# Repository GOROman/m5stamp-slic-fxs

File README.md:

# m5stamp-slic-fxs — SLIC2PORT-FXS

**ステータス: 基板 v4.0（4層・全面再レイアウト・KiCad 配線済み）が最新。未発注。2026-10-31 時点**

**v4.0** は、v3.4.2 の電気的中身（回路・ネット・156 部品）をそのままに、配置を全面刷新して **4 層化**（F.Cu 信号 / In1.Cu GND プレーン / In2.Cu 信号 / B.Cu 信号）し、KiCad 上で配線まで完遂した版です。機能ブロック構成（ポート A/B を左右対称に、SLIC は自ポート近く、リレーは同一方向に整列、Stamp は中央＋アンテナキープアウト）で、FreeRouting + 手仕上げにより**未接続 0・短絡 0**。DRC の残件はフットプリント固有の裁定済み項目のみです。製造用 Gerber は KiCad 出力の一式を `gerber/` に同梱しています。**推奨ソルダーマスク色はマットブラック**（発注時に選択）。シルクにはタイトルブロック「SLIC2PORT-FXS Rev 4.0 / @GOROman / 2026-10-31」、大型部品の機能名ラベル、回線系エリアへの高圧警告マークを入れ、ロゴは決定後に差し替えできるよう配置スペースを確保しています。詳細は `kicad/CAD_REPORT.md` 第11ラウンド参照。

v3.4 は第7ラウンドの全数監査（物理干渉・シルク・ファームウェア整合・電気的妥当性・製造性・調達整合・極性）を通過して EasyEDA で配線した版（配線率 100%、トラック 1,514 本・ビア 179 本）、v3.4.1 は発注前チェック（Issue #9・#12）の是正版、v3.4.2 は RJ11 を秋月 100954（Neltron 7002-XPXC）のメーカー図面で全面是正し C13 のパッド干渉を解消した版です。各版の経緯は `kicad/CAD_REPORT.md` 第7〜第10ラウンドと Git 履歴を参照してください。v3.4 の EasyEDA 配線データ（`gerber/SLIC2PORT-FXS-v3.4.epro2` 等）は履歴として残しています。

## 概要

FAX機（Canon PIXUS MX923）と PC の FAXモデム（または2台目の FAX/電話機）を、公衆回線なしで直接 T.30 通信させるための、M5Stamp 制御の **2ポート疑似交換機（FXS 回線シミュレータ）** 基板の設計プロジェクト。

- SLICモジュール **KS0835F（Silvertel AG1171 系）×2** をソケット搭載し、各ポートが独立した加入者回線として振る舞う（回線電圧供給・リング送出/リングトリップ・オフフック検出）
- 制御は **M5StampS3（ESP32-S3）**：状態機械（発信/呼出/接続/解放）、ADC による音声モニタ＋DTMF（Goertzel）検出、トーン生成
- 音声のクロス接続は **Omron G5V-2 リレー×2**（DPDT）。無励磁（フェイルセーフ）で相手ポートと相互接続、励磁でトーンバスに切り替わる
- 信号レベルの不整合（SLIC 5V 系 ⇔ ESP32-S3 3.3V 系）は **74HCT244** のレベル変換と SHK 分圧で吸収
- ポートAに FAX機、ポートBにモデムを RJ11 で挿すだけで相互に発着信でき、T.30 ハンドシェイクがそのまま通る想定

## 基板プレビュー（v4.0・配線済み）

KiCad で全面再レイアウト・配線した v4.0 のレンダリングです。象限ズームは `docs/images/board-v40-crop-q1.png` 〜 `board-v40-crop-q4.png`。旧版（v3.4 配線済み・配置版ほか）も `docs/images/` に収蔵しています。

v3.4 までの歩み: v3.1 でパスコンを負荷近傍へ是正（C10 は U1 ソケット直下の裏面配置）、v3.2 で動作チェック用ステータス LED ×6 を追加、v3.3 で KiCad 標準の番号付きネット形式に是正（EasyEDA がネットを読めるようにする変換。経緯は CAD_REPORT 第6ラウンド）、v3.4 で全数監査の是正（端子台 J2 と U2 の物理干渉解消、シルク全数 225 テキストを干渉ゼロに再配置、RJ11 と Stamp ソケットの環状銅箔を JLCPCB 2層の製造下限以上に拡大、PD ダイオードを 1N5819 に変更、裏面警告文を移設）を行いました。その後 v3.4.1（発注前チェック是正）、v3.4.2（RJ11 の秋月 100954 実寸是正 + C13 のパッド干渉解消）を経て、v4.0 で全面再レイアウト + 4層化 + KiCad 配線を行いました。詳細は `kicad/CAD_REPORT.md` 第6〜第11ラウンド参照。

## 基板上の部品: 必須 / なくても動く

実装時の判断用に、基板上の部品を「ないと動かない（必須）」と「なくても動く（デバッグ・確認用／任意）」に分けました。部品番号は `bom.csv` / 基板 v3.4 のものです。

### 必須（ないと交換機として動かない）

| グループ | 部品 | 理由 |
|---|---|---|
| SLIC インターフェース | MOD_A, MOD_B（KS0835F）、RJ11 ジャック J_3, J_4 | 回線そのもの。TIP/RING の供給・リング送出・オフフック検出を担う |
| 制御・レベル変換 | U1（M5StampS3・ソケット実装）、U2（74HCT244） | 状態機械本体。HCT244 は F/R・RM・SEL・TONE を 5V フルスイングへ変換し、ないと SLIC の VIH を満たせない |
| SHK 取り込み | 10K/18K 分圧＋1nF（各ポート） | SHK 出力（約4.5V）を ESP32-S3 の入力範囲へ落とす。過電圧対策を兼ねる |
| 音声クロス接続 | K1, K2（G5V-2 リレー）、Q3, Q4（2N7002 ドライバ）、還流用 1N4007×2、ゲートプルダウン | VX/VR の相互接続とトーンバス切替。無励磁=クロス接続のフェイルセーフ構成 |
| 音声パス | 結合・バイアス用 100nF / 100K 群、0R（R20, R28: レベル調整用パッド、初期値 0Ω 実装） | VX/VR の AC 結合と VAUD バイアス。DTMF 受信用の ADC タップ（MON_x: 100nF＋100K＋10K＋1nF）もここに含まれ、ダイヤル検出に必須 |
| トーン生成 | LEDC 出力の RC ローパス（10K＋47nF ×2段）、47K 注入抵抗（R11）、100nF 直列結合 | ダイヤルトーン/呼出音/話中音（400Hz）をトーンバスへ注入する経路 |
| 電源 | J1（USB-C・CC 5.1K プルダウン含む）または J2（端子台）のいずれか一方＋両方実装が標準、F1（ポリヒューズ 2A）、Q1（AO3401A 逆接保護）、D1（SMBJ5.0A TVS）、C1（1000µF） | 5V 入力と保護。同時給電は禁止（どちらか一方から給電） |
| ポート電源 | フェライトビーズ U64, U91、C13, C22（470µF）、モジュール直近 100nF | AG1171 接続図指定のモジュール電源まわり。DC/DC ノイズのポート間回り込み防止 |
| 回線保護 | P3100SC（U55, U82）、保護ブリッジ 1N4007×8、BZT03C82（U60, U87）、27K CLI バイアス（R16, R24）、10nF/250V EMI コンデンサ（C11, C12, C20, C21） | いずれも AG1171 データシート指定の回線側構成。サージのクランプ（v3.4.1 でメーカー図の GND 基準クランプに是正）とオンフック時 DC 経路 |
| リセットプルダウン | 100K ×7（HCT244 の使用入力分）ほか信号プルダウン群 | ESP32 のリセット・書き込み中も RM/SEL/TONE/F/R を L に確定させるため |
| 基準電圧 | VAUD 分圧（4.7K×2＋10µF＋100nF）、VREF165 分圧（47K×2） | 音声バイアス（約2.5V）と ADC タップのバイアス（約1.65V） |
| パスコン | 各 IC・モジュール近傍の 100nF 群（C6, C10, C14, C23 ほか） | 発振・誤動作防止。配置は負荷近傍に最適化済み（v3.1/v3.4） |
| 操作ボタン | SW1（RST）, SW2（BOOT） | リセットと書き込みモード操作用。v3.4.1 で SW2 を移動し、パッド間隔 1.8mm を確保済み（v3.4 では接触していた。Issue #9） |

### なくても動く（未実装でも交換機として動作する）

| グループ | 部品 | 用途 |
|---|---|---|
| ステータス LED 群 | D2（電源）, D3（GPIO4 ステータス）, D4〜D9（HOOK/RING/LINK・ポート毎）と R_LED1〜R_LED8、HOOK 表示バッファ Q5, Q6（2N7002） | 通電状態と各ポートのオフフック/リング/リレー励磁を目視確認するための表示専用（DESIGN §5.7） |
| テストポイント | TP1〜TP34 | 主要信号の引き出しランド（ピンヘッダ兼用）。部品実体はない。TP4/TP5/TP12/TP13（TIP/RING）は高電圧注意 |
| PD 引き下げ回路 | 1N5819（U79, U106）、Q2（2N7002）と PD バスまわり | SLIC のパワーダウン用。デフォルトはオープン（常時起動）で、v1 ファームウェアでは未使用。回路だけ用意してある |
| デバッグ・拡張コネクタ | J6（UART_DBG）, J5（EXPANSION） | シリアルデバッグと将来拡張用 |

## 必要なパーツ（基板の外も含む）

### 必須

| パーツ | 備考 |
|---|---|
| 本基板（v4.0 を発注） | JLCPCB 想定、4層 1oz。ソルダーマスク色は**マットブラック推奨**（発注時に選択） |
| KS0835F モジュール ×2 | 標準バリアント（3.2〜5.5V・0dB）。ユーザ所有品から使用 |
| M5StampS3（または S3A）×1 | 基板側に 1.27mm ピッチ メスピンヘッダ 17P＋11P を実装し、Stamp 側キャスタレーションにオスピンを付けて差し込む（直接はんだ付けしない） |
| KS0835F 用ソケット/ピンヘッダ | モジュールもソケット実装（2.54mm ピッチ、ピン5–6間にギャップあり） |
| 5V/3A 電源 | 最悪消費 約1.5A の設計。USB 2.0 ポート給電では不足。通常の USB-C 5V アダプタか端子台から給電 |
| RJ11（6P6C・中央ペア結線）ケーブル ×2 | FAX機・モデムとの接続用。日本の 6極2芯コードも中央ペアなのでそのまま使える |
| 上記「必須」表の基板実装部品一式 | 詳細は `bom.csv`（調達先の型番メモは Note 欄） |

### オプション（あると良いもの）

| パーツ | 用途 |
|---|---|
| FAXモデム（USB/シリアル）または 2台目の FAX機・電話機 | ポートB 側の対向試験用。本命は Canon PIXUS MX923 との T.30 対向 |
| オシロスコープ / ロジックアナライザ | リング波形（20Hz・135Vp-p）と T.30 ハンドシェイクの観測。テストポイントが全信号分あるので効く |
| 3Dプリントケース | `enclosure/` に設計予定（現在設計中） |
| 秋月電子の簡易擬似電話交換機キット | 本基板なしでも FAX 同士を繋げる比較・切り分け用リグ |
| 予備の KS0835F モジュール | 故障切り分け用（所有 4 個のうち 2 個を本基板に使用） |
| ピンヘッダ（TP 用） | テストポイントに常設プローブ点を付けたい場合 |

## ファームウェア

- `firmware/m5stamp_fxs_exchange.ino`＋`firmware/platformio.ini`。PlatformIO（espressif32@7.0.1 固定）で `pio run -d firmware` の成功を確認済み。LEDC API は Arduino core 2.x/3.x 両対応の互換シム入り
- GitHub Actions の CI（regression＋firmware-build 実ビルド）は緑
- DTMF 受信は最短 40ms のトーンに対応（スライディングウィンドウ方式。要件は DESIGN §8.4、検証は Issue #7）
- リング試験後の誤発呼（Issue #5）、PlatformIO と Arduino API の不整合（#4）は修正済み。Issue #4〜#7 はいずれもクローズ

## ケース

3Dプリント用ケースは設計中です（`enclosure/` に配置予定）。基板 120×90mm・取付穴 4 点に合わせ、RJ11/USB-C/端子台の開口と LED 窓を持つ 2 ピース構成を想定しています。

## 内容物

| パス | 内容 |
|---|---|
| `DESIGN.md` | 設計書本体（ブロック図、電源・保護設計、GPIO 割り当て、音声クロス接続とトーンの定数設計、動作シーケンス、レイアウト指針、実物確認手順、DTMF 仕様 §8.4） |
| `bom.csv` | 部品表（156点・43グループ、ネットリストから生成。TP 34 点を含む） |
| `firmware/` | M5StampS3 用制御スケッチと PlatformIO 設定 |
| `kicad/` | SKiDL 回路定義（`skidl/`、ネットリスト含む）、自作フットプリント（KS0835F・RJ11・Stamp ソケット）、基板データ `SLIC2PORT-FXS.kicad_pcb`（v4.0・配線済み）、`CAD_REPORT.md`（設計・監査の記録）、`README_CAD.md` |
| `gerber/` | v4.0 の製造データ: `SLIC2PORT-FXS-v4.0-gerber-kicad.zip`（KiCad 出力の Gerber 一式）と個別ファイル一式。v3.4 の EasyEDA データ（`SLIC2PORT-FXS-v3.4-gerber-easyeda.zip`、`SLIC2PORT-FXS-v3.4.epro2`）も履歴として収蔵 |
| `docs/images/` | 基板レンダリング（配線済み v4.0: `board-v40-routed-{top,bottom,3d}.png`、象限ズーム `board-v40-crop-q1..q4.png`、旧版も収蔵） |
| `tests/` | ホスト回帰テスト（状態機械・DTMF・ハードウェア整合） |
| `research/` | 参照資料: AG1171 データシート、KS0835F データシート（PDF＋テキスト抽出） |
| レビュー記録 | 修正点・残課題は [`REVIEW.md`](REVIEW.md) と GitHub Issues を参照 |

## 発注前に必須の確認（設計書 §10）

- v4.0 の Gerber（`gerber/SLIC2PORT-FXS-v4.0-gerber-kicad.zip`）で発注すること。注文オプションは **4層**、ソルダーマスク色は**マットブラック推奨**
- 実物 KS0835F モジュールのバリアント刻印の確認
- モジュールのピン間隔（5ピン＋6ピンの2クラスタ、ピン5–6間ギャップ）のノギス実測 → フットプリントのパラメータ検証
- 実 RJ11（秋月 100954）現物で嵌合・ペグ入りを最終確認すること（フットプリントはメーカー図面で是正済み: 接点穴 ø0.90・位置決めペグ NPTH ø2.30 ×2）
- `enclosure/` の開口は v3.4 系の配置前提のため v4.0 のコネクタ位置には合わない。ケースを使う場合は enclosure 側の改修が必要

## 安全上の注意

- **公衆電話回線（PSTN）への接続は絶対禁止**。ローカル閉回線専用です（基板シルクにも明記）。
- リング時は回線に最大約 135Vp-p が出ます。感電に注意してください。
- 5.5V を超える無調整電源の直結は厳禁です（KS0835F の絶対最大定格）。

## 参考にした先行事例

- Silvertel AG1171 Datasheet／KS0835F Datasheet V1.3（`research/` に同梱）
- GitHub `diggydude/php-pbx`（KS0835F を使った電話交換機の実例）
- 秋月電子 簡易擬似電話交換機キット（リレー式通話路の構成を参考）
- M5Stack 公式ドキュメント・公式 GitHub `M5_Hardware`（Stamp-S3 のシンボル/フットプリント）

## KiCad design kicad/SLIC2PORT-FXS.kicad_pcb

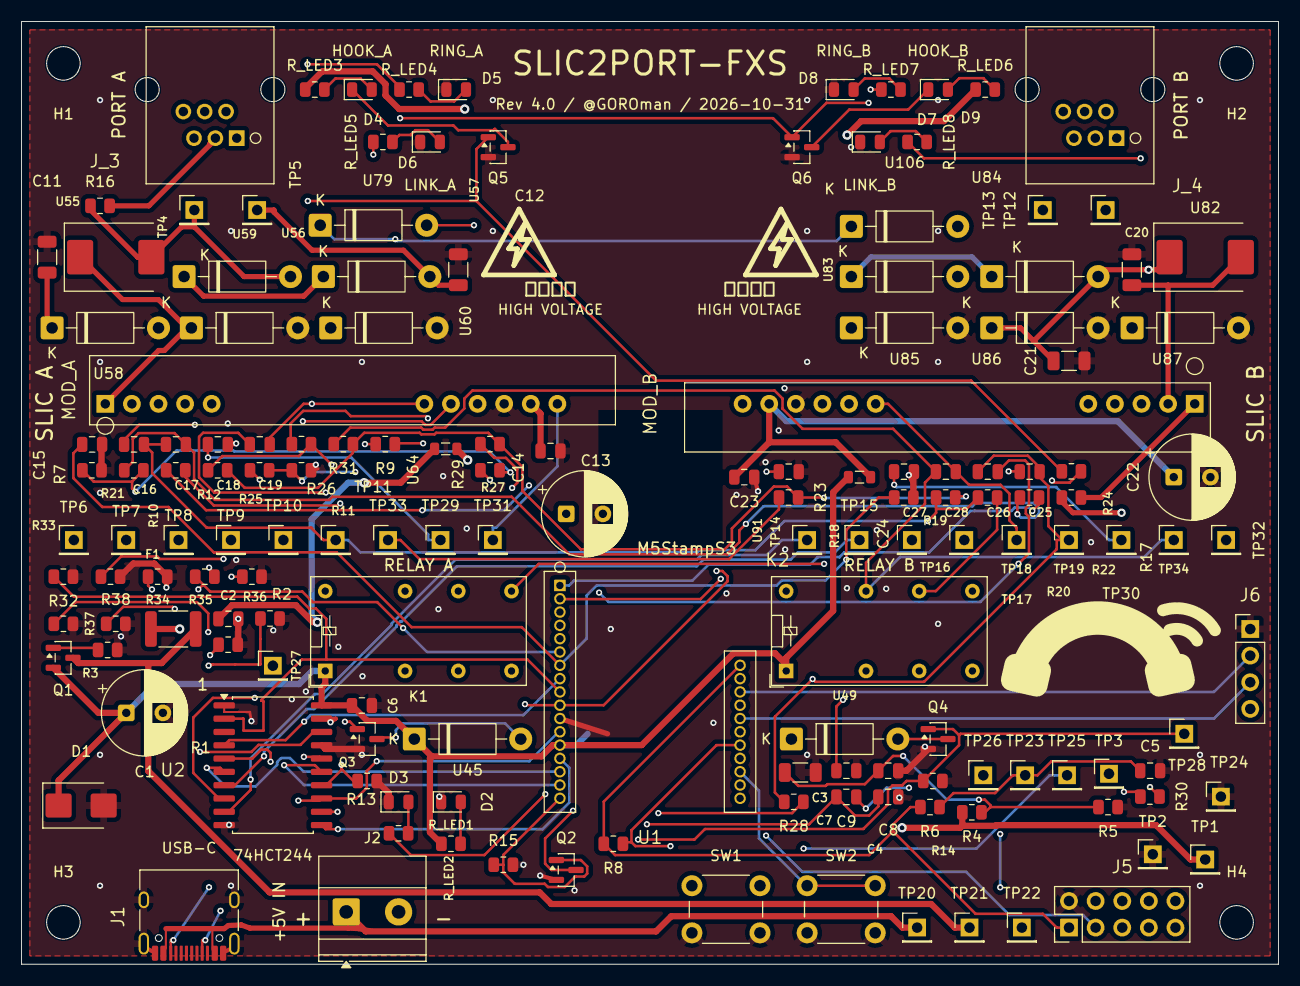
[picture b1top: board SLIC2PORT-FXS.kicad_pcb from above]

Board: 4 copper layers, 120.0 x 90.0 mm, 160 parts (1 on the bottom side), 82 nets.

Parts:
C1: 1000uF/10V; CP_Radial_D8.0mm_P3.50mm
C2, C4, C5, C6, C9, C10, C14, C16, C17, C19, C23, C25, C26, C28: 100nF; C_0805_2012Metric
C3: 10uF; C_1206_3216Metric
C7, C8: 47nF; C_0805_2012Metric
C11, C12, C20, C21: 10nF; C_1206_3216Metric
C13, C22: 470uF/10V; CP_Radial_D8.0mm_P3.50mm
C15, C18, C24, C27: 1nF; C_0805_2012Metric
D1: SMBJ5.0A; D_SMB
D2: LED_RED; LED_0805_2012Metric
D3, D4, D7: LED_GRN; LED_0805_2012Metric
D5, D8: LED_YEL; LED_0805_2012Metric
D6, D9: LED_BLU; LED_0805_2012Metric
F1: Polyfuse_2A; Fuse_1812_4532Metric
H1, H2, H3, H4: MountingHole_3.2mm_M3
J1: USB-C_PWR; USB_C_Receptacle_HRO_TYPE-C-31-M-12
J2: DC5V_IN; TerminalBlock_Phoenix_MKDS-1,5-2_1x02_P5.00mm_Horizontal
J5: EXPANSION; PinHeader_2x05_P2.54mm_Vertical
J6: UART_DBG; PinHeader_1x04_P2.54mm_Vertical
J_3, J_4: RJ11_6P6C; RJ11_6P6C_TH
K1, K2: G5V-2_DC5; Relay_DPDT_Omron_G5V-2
MOD_A: KS0835F
MOD_B: KS0835F
Q1: AO3401A; SOT-23
Q2, Q3, Q4, Q5, Q6: 2N7002; SOT-23
R1, R2: 5.1K; R_0805_2012Metric
R3, R12, R13, R14, R15, R19, R21, R23, R27, R29, R31, R32, R33, R34, R35, R36, R37, R38: 100K; R_0805_2012Metric
R4, R5: 4.7K; R_0805_2012Metric
R6, R7, R11: 47K; R_0805_2012Metric
R8, R9, R10, R17, R22, R25, R30: 10K; R_0805_2012Metric
R16, R24: 27K; R_0805_2012Metric
R18, R26: 18K; R_0805_2012Metric
R20, R28: 0R; R_0805_2012Metric
R_LED1, R_LED5, R_LED8: 1K; R_0805_2012Metric
R_LED2: 470; R_0805_2012Metric
R_LED3, R_LED4, R_LED6, R_LED7: 1.5K; R_0805_2012Metric
SW1: RST; SW_PUSH_6mm
SW2: BOOT; SW_PUSH_6mm
TP1: +5V; PinHeader_1x01_P2.54mm_Vertical
TP2, TP24: GND; PinHeader_1x01_P2.54mm_Vertical
TP3: TONE_BUS; PinHeader_1x01_P2.54mm_Vertical
TP4: TIP_A; PinHeader_1x01_P2.54mm_Vertical
TP5: RING_A; PinHeader_1x01_P2.54mm_Vertical
TP6: FR_A_5V; PinHeader_1x01_P2.54mm_Vertical
TP7: RM_A_5V; PinHeader_1x01_P2.54mm_Vertical
TP8: SHK_A_RAW; PinHeader_1x01_P2.54mm_Vertical
TP9: VX_A_PIN; PinHeader_1x01_P2.54mm_Vertical
TP10: VR_A_PIN; PinHeader_1x01_P2.54mm_Vertical
TP11: VX_A_AUD; PinHeader_1x01_P2.54mm_Vertical
TP12: TIP_B; PinHeader_1x01_P2.54mm_Vertical
TP13: RING_B; PinHeader_1x01_P2.54mm_Vertical
TP14: FR_B_5V; PinHeader_1x01_P2.54mm_Vertical
TP15: RM_B_5V; PinHeader_1x01_P2.54mm_Vertical
TP16: SHK_B_RAW; PinHeader_1x01_P2.54mm_Vertical
TP17: VX_B_PIN; PinHeader_1x01_P2.54mm_Vertical
TP18: VR_B_PIN; PinHeader_1x01_P2.54mm_Vertical
TP19: VX_B_AUD; PinHeader_1x01_P2.54mm_Vertical
TP20: VIN_RAW; PinHeader_1x01_P2.54mm_Vertical
TP21: VIN_F; PinHeader_1x01_P2.54mm_Vertical
TP22: VAUD; PinHeader_1x01_P2.54mm_Vertical
TP23: VREF165; PinHeader_1x01_P2.54mm_Vertical
TP25: TONE_5V; PinHeader_1x01_P2.54mm_Vertical
TP26: TONE_AC; PinHeader_1x01_P2.54mm_Vertical
TP27: SEL_A_5V; PinHeader_1x01_P2.54mm_Vertical
TP28: SEL_B_5V; PinHeader_1x01_P2.54mm_Vertical
TP29: MON_A; PinHeader_1x01_P2.54mm_Vertical
TP30: MON_B; PinHeader_1x01_P2.54mm_Vertical
TP31: PD_A; PinHeader_1x01_P2.54mm_Vertical
TP32: PD_B; PinHeader_1x01_P2.54mm_Vertical
TP33: VR_A_IN; PinHeader_1x01_P2.54mm_Vertical
TP34: VR_B_IN; PinHeader_1x01_P2.54mm_Vertical
U1: M5StampS3/S3A; Stamp-S3-Socket
U2: 74HCT244; SOIC-20W_7.5x12.8mm_P1.27mm
U45, U49, U56, U57, U58, U59, U83, U84, U85, U86: 1N4007; D_DO-41_SOD81_P10.16mm_Horizontal
U55, U82: P3100SC; D_SMC
U60, U87: BZT03C82; D_DO-41_SOD81_P10.16mm_Horizontal
U64, U91: BK2125HS601-T; L_0805_2012Metric
U79, U106: 1N5819; D_DO-41_SOD81_P10.16mm_Horizontal

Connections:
+3V3: J5.1, J6.4, R6.1, R8.1, U1.28
+5V: C1.1, C2.1, C6.1, C10.1, D1.1, K1.1, K2.1, Q1.2, R4.1, R_LED1.1, TP1.1, U1.13, U2.20, U45.1, U49.1, U64.1, U91.1
+5V_PA: C13.1, C14.1, MOD_A.10, R_LED3.1, U64.2
+5V_PB: C22.1, C23.1, MOD_B.10, R_LED6.1, U91.2
BRP_A: U56.1, U57.1, U60.1
BRP_B: U83.1, U84.1, U87.1
EN: R8.2, SW1.1, U1.22
FR_A_5V: MOD_A.3, TP6.1, U2.18
FR_A_33: R32.1, U1.9, U2.2
FR_B_5V: MOD_B.3, TP14.1, U2.9
FR_B_33: R36.1, U1.14, U2.11
GND: C1.2, C2.2, C3.2, C4.2, C5.2, C6.2, C7.2, C8.2, C10.2, C11.2, C12.2, C13.2, C14.2, C15.2, C18.2, C20.2, C21.2, C22.2, C23.2, C24.2, C27.2, D1.2, D2.1, D3.1, D5.1, D6.1, D8.1, D9.1, J1.A1, J1.A12, J1.B1, J1.B12, J1.SH, J2.2, J5.2, J6.1, MOD_A.9, MOD_B.9, Q2.2, Q3.2, Q4.2, Q5.2, Q6.2, R1.2, R2.2, R3.2, R5.2, R7.2, R13.2, R14.2, R15.2, R18.2, R26.2, R32.2, R33.2, R34.2, R35.2, R36.2, R37.2, R38.2, SW1.2, SW2.2, TP2.1, TP24.1, U1.11, U1.18, U2.1, U2.10, U2.17, U2.19, U58.2, U59.2, U60.2, U85.2, U86.2, U87.2
GPIO0: SW2.1, U1.20
GPIO3: J5.10, U1.3
GPIO4: J5.3, R_LED2.1, U1.4
GPIO5: J5.4, U1.5
GPIO39: J5.5, U1.19
GPIO40: J5.6, U1.21
GPIO41: J5.7, U1.23
GPIO42: J5.8, U1.25
GPIO43: J6.2, U1.26
GPIO44: J6.3, U1.24
GPIO46: J5.9, U1.27
HK_A_DRV: D4.1, Q5.3
HK_B_DRV: D7.1, Q6.3
LED_HK_A: D4.2, R_LED3.2
LED_HK_B: D7.2, R_LED6.2
LED_LK_A: D6.2, R_LED5.2
LED_LK_B: D9.2, R_LED8.2
LED_PWR_A: D2.2, R_LED1.2
LED_RG_A: D5.2, R_LED4.2
LED_RG_B: D8.2, R_LED7.2
LED_ST_A: D3.2, R_LED2.2
MON_A: C18.1, R22.2, TP29.1, U1.1
MON_B: C27.1, R30.2, TP30.1, U1.2
unnamed: J1.A5, R1.1
unnamed: J1.B5, R2.1
PD_A: MOD_A.11, TP31.1, U79.2
PD_B: MOD_B.11, TP32.1, U106.2
PD_BUS: Q2.3, U79.1, U106.1
PD_EN: Q2.1, R15.1, U1.17
Q1_GATE: Q1.1, R3.1
RING_A: C12.1, J_3.3, MOD_A.1, R16.2, TP5.1, U55.1, U57.2, U59.1
RING_B: C21.1, J_4.3, MOD_B.1, R24.2, TP13.1, U82.1, U84.2, U86.1
RLY_A_COIL: K1.16, Q3.3, U45.2
RLY_B_COIL: K2.16, Q4.3, U49.2
RM_A_5V: MOD_A.4, R_LED4.1, TP7.1, U2.16
RM_A_33: R33.1, U1.8, U2.4
RM_B_5V: MOD_B.4, R_LED7.1, TP15.1, U2.7
RM_B_33: R37.1, U1.12, U2.13
SEL_A_5V: Q3.1, R13.1, R_LED5.1, TP27.1, U2.14
SEL_A_33: R34.1, U1.15, U2.6
SEL_B_5V: Q4.1, R14.1, R_LED8.1, TP28.1, U2.5
SEL_B_33: R38.1, U1.16, U2.15
SHK_A_33: C15.1, R17.2, R18.1, U1.7
SHK_A_RAW: MOD_A.5, Q5.1, R17.1, TP8.1
SHK_B_33: C24.1, R25.2, R26.1, U1.10
SHK_B_RAW: MOD_B.5, Q6.1, R25.1, TP16.1
TAP_A_N: C17.2, R21.1, R22.1
TAP_B_N: C26.2, R29.1, R30.1
TIP_A: C11.1, J_3.4, MOD_A.2, R16.1, TP4.1, U55.2, U56.2, U58.1
TIP_B: C20.1, J_4.4, MOD_B.2, R24.1, TP12.1, U82.2, U83.2, U85.1
TONE_5V: R9.1, TP25.1, U2.12
TONE_AC: C9.2, R11.1, TP26.1
TONE_BUS: K1.8, K1.9, K2.8, K2.9, R11.2, R12.1, TP3.1
TONE_N1: C7.1, R9.2, R10.1
TONE_N2: C8.1, C9.1, R10.2
TONE_PWM_33: R35.1, U1.6, U2.8
VAUD: C3.1, C4.1, R4.2, R5.1, R12.2, R19.2, R23.2, R27.2, R31.2, TP22.1
VIN_F: F1.2, Q1.3, TP21.1
VIN_RAW: F1.1, J1.A4, J1.A9, J1.B4, J1.B9, J2.1, TP20.1
VREF165: C5.1, R6.2, R7.1, R21.2, R29.2, TP23.1
VR_A_IN: C19.1, K1.4, K1.13, R23.1, TP33.1
VR_A_PIN: C19.2, MOD_A.6, TP10.1
VR_B_IN: C28.1, K2.4, K2.13, R31.1, TP34.1
VR_B_PIN: C28.2, MOD_B.6, TP18.1
VX_A_AUD: C16.2, C17.1, R19.1, R20.1, TP11.1
VX_A_IN: K2.6, K2.11, R20.2
VX_A_PIN: C16.1, MOD_A.7, TP9.1
VX_B_AUD: C25.2, C26.1, R27.1, R28.1, TP19.1
VX_B_IN: K1.6, K1.11, R28.2
VX_B_PIN: C25.1, MOD_B.7, TP17.1

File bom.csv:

Value,Footprint,Qty,Refs,Note
0R,Resistor_SMD:R_0805_2012Metric,2,R20 R28,
1.5K,Resistor_SMD:R_0805_2012Metric,4,R_LED3 R_LED4 R_LED6 R_LED7,ステータス LED 電流制限 (HOOK/RING、約2mA)
1000uF/10V,Capacitor_THT:CP_Radial_D8.0mm_P3.50mm,1,C1,入力バルク。缶径 Ø8.0mm 品が必須 (Ø10mm 品は R30 と干渉。CAD_REPORT 第9ラウンド注記参照)
100K,Resistor_SMD:R_0805_2012Metric,18,R12 R13 R14 R15 R19 R21 R23 R27 R29 R3 R31 R32 R33 R34 R35 R36 R37 R38,
100nF,Capacitor_SMD:C_0805_2012Metric,14,C10 C14 C16 C17 C19 C2 C23 C25 C26 C28 C4 C5 C6 C9,
10K,Resistor_SMD:R_0805_2012Metric,7,R10 R17 R22 R25 R30 R8 R9,
10nF,Capacitor_SMD:C_1206_3216Metric,4,C11 C12 C20 C21,EMI 対策 (AG1171)。250V 耐圧品を使うこと
10uF,Capacitor_SMD:C_1206_3216Metric,1,C3,
18K,Resistor_SMD:R_0805_2012Metric,2,R18 R26,
1K,Resistor_SMD:R_0805_2012Metric,3,R_LED1 R_LED5 R_LED8,LED 電流制限 (R_LED1=電源 LED、R_LED5/R_LED8=LINK)
1N4007,Diode_THT:D_DO-41_SOD81_P10.16mm_Horizontal,10,U45 U49 U56 U57 U58 U59 U83 U84 U85 U86,保護ブリッジ x4/ポート + リレー還流 x2 (秋月 100934)。PD 用は 1N5819 行に分離 (v3.4)
1N5819,Diode_THT:D_DO-41_SOD81_P10.16mm_Horizontal,2,U106 U79,PD 引き下げ用ショットキー。Vf が低く Ag1171 の PD VIL(max) 0.5V を満たすため v3.4 で 1N4007 から変更
1nF,Capacitor_SMD:C_0805_2012Metric,4,C15 C18 C24 C27,
27K,Resistor_SMD:R_0805_2012Metric,2,R16 R24,CLI バイアス (指定 20K-39K)
2N7002,Package_TO_SOT_SMD:SOT-23,5,Q2 Q3 Q4 Q5 Q6,PD 引き下げ (Q2) + リレードライバ (Q3/Q4) + HOOK LED バッファ (Q5/Q6)
4.7K,Resistor_SMD:R_0805_2012Metric,2,R4 R5,
470,Resistor_SMD:R_0805_2012Metric,1,R_LED2,
470uF/10V,Capacitor_THT:CP_Radial_D8.0mm_P3.50mm,2,C13 C22,モジュール直近 (KS0835F 接続図 C5)
47K,Resistor_SMD:R_0805_2012Metric,3,R11 R6 R7,
47nF,Capacitor_SMD:C_0805_2012Metric,2,C7 C8,
5.1K,Resistor_SMD:R_0805_2012Metric,2,R1 R2,
74HCT244,Package_SO:SOIC-20W_7.5x12.8mm_P1.27mm,1,U2,"レベル変換 3.3V->5V (F/R, RM, SEL, TONE)"
AO3401A,Package_TO_SOT_SMD:SOT-23,1,Q1,逆接保護 P-FET
BK2125HS601-T,Inductor_SMD:L_0805_2012Metric,2,U64 U91,フェライトビーズ 600ohm@100MHz (秋月 109506)。BLM21AG601 でも可
BOOT,Button_Switch_THT:SW_PUSH_6mm,1,SW2,
BZT03C82,Diode_THT:D_DO-41_SOD81_P10.16mm_Horizontal,2,U60 U87,ブリッジ対角クランプ。P6KE82 でも可
DC5V_IN,"TerminalBlock_Phoenix:TerminalBlock_Phoenix_MKDS-1,5-2_1x02_P5.00mm_Horizontal",1,J2,端子台は 5.00mm ピッチ品 (秋月 WJ301-5.0-02P) を使用。KF301 (5.08mm) はピッチ不一致で不可。USB-C と同時給電禁止
EXPANSION,Connector_PinHeader_2.54mm:PinHeader_2x05_P2.54mm_Vertical,1,J5,
G5V-2_DC5,Relay_THT:Relay_DPDT_Omron_G5V-2,2,K1 K2,音声クロス接続リレー (Omron G5V-2 DC5)。マルツ取扱い
KS0835F,SLIC2PORT:KS0835F,2,MOD_A MOD_B,ユーザ所有品 x4 のうち 2 個使用。ソケット実装
LED_BLU,LED_SMD:LED_0805_2012Metric,2,D6 D9,青: LINK (リレー励磁) 表示 (§5.7)
LED_GRN,LED_SMD:LED_0805_2012Metric,3,D3 D4 D7,緑: D3=ステータス (GPIO4)、D4/D7=HOOK 表示 (§5.7)
LED_RED,LED_SMD:LED_0805_2012Metric,1,D2,電源 LED
LED_YEL,LED_SMD:LED_0805_2012Metric,2,D5 D8,黄: RING 表示 (§5.7)
M5StampS3/S3A,SLIC2PORT:Stamp-S3-Socket,1,U1,ユーザ調達。ソケット実装 (直接はんだ付けしない): 基板側に 1.27mmピッチ メスピンヘッダ 17P + 11P (分割可能なソケットレールで可) を実装し、Stamp 側キャスタレーションに 1.27mm オスピンを付けて差し込む。PIN2.54 バリアント不可
P3100SC,Diode_SMD:D_SMC,2,U55 U82,回線保護サイリスタ (差動)。P3100EBL (TO-92) でも可
Polyfuse_2A,Fuse:Fuse_1812_4532Metric,1,F1,例: Littelfuse 1812L200 相当
RJ11_6P6C,SLIC2PORT:RJ11_6P6C_TH,2,J_3 J_4,"中央ペア (pin3=RING, pin4=TIP) のみ使用。指定部品: 秋月電子 100954 (Neltron 7002-6P6C)"
RST,Button_Switch_THT:SW_PUSH_6mm,1,SW1,
SMBJ5.0A,Diode_SMD:D_SMB,1,D1,5V 入力 TVS
TP,Connector_PinHeader_2.54mm:PinHeader_1x01_P2.54mm_Vertical,34,TP1 TP10 TP11 TP12 TP13 TP14 TP15 TP16 TP17 TP18 TP19 TP2 TP20 TP21 TP22 TP23 TP24 TP25 TP26 TP27 TP28 TP29 TP3 TP30 TP31 TP32 TP33 TP34 TP4 TP5 TP6 TP7 TP8 TP9,テストポイント (TP1-TP34)。TIP/RING は高電圧注意
UART_DBG,Connector_PinHeader_2.54mm:PinHeader_1x04_P2.54mm_Vertical,1,J6,
USB-C_PWR,Connector_USB:USB_C_Receptacle_HRO_TYPE-C-31-M-12,1,J1,電源専用。CC に 5.1K プルダウン済

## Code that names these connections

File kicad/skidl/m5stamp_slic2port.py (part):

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FR_A_33  = mknet("FR_A_33");  FR_B_33 = mknet("FR_B_33")
SEL_A_33 = mknet("SEL_A_33"); SEL_B_33 = mknet("SEL_B_33")
PD_EN    = mknet("PD_EN")
GPIO0    = mknet("GPIO0");    EN_NET = mknet("EN")
GPIO3    = mknet("GPIO3");    GPIO4 = mknet("GPIO4"); GPIO5 = mknet("GPIO5")
GPIO39   = mknet("GPIO39");   GPIO40 = mknet("GPIO40")
GPIO41   = mknet("GPIO41");   GPIO42 = mknet("GPIO42"); GPIO46 = mknet("GPIO46")
GPIO43   = mknet("GPIO43");   GPIO44 = mknet("GPIO44")

MON_A += u1["G1"];   MON_B += u1["G2"]
GPIO3 += u1["G3"];   GPIO4 += u1["G4"];  GPIO5 += u1["G5"]
TONE33 += u1["G6"]
SHK_A_33 += u1["G7"];  RM_A_33 += u1["G8"];  FR_A_33 += u1["G9"]
SHK_B_33 += u1["G10"]; RM_B_33 += u1["G11"]; FR_B_33 += u1["G12"]
SEL_A_33 += u1["G13"]; SEL_B_33 += u1["G14"]; PD_EN += u1["G15"]
GPIO39 += u1["G39"]; GPIO0 += u1["G0"]; GPIO40 += u1["G40"]
EN_NET += u1["EN"];  GPIO41 += u1["G41"]; GPIO44 += u1["G44"]
GPIO42 += u1["G42"]; GPIO43 += u1["G43"]; GPIO46 += u1["G46"]

# EN プルアップ + リセット/ブート スイッチ
between(R("10K"), P3V3, EN_NET)
sw_rst = TACT(); sw_rst.ref = "SW1"; sw_rst.value = "RST"
between(sw_rst, EN_NET, GND)
sw_boot = TACT(); sw_boot.ref = "SW2"; sw_boot.value = "BOOT"
between(sw_boot, GPIO0, GND)

# ステータス LED (GPIO4) / 電源 LED
n_leda = Net("LED_ST_A")
r_led2 = R("470", ref="R_LED2")
GPIO4 += r_led2[1]
n_leda += r_led2[2]
d_led2 = LED(); d_led2.ref = "D3"; d_led2.value = "LED_GRN"
n_leda += d_led2["A"]; GND += d_led2["K"]
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
# 拡張 / デバッグ ヘッダ
j_exp = HDR2X5(); j_exp.ref = "J5"; j_exp.value = "EXPANSION"
P3V3 += j_exp[1]; GND += j_exp[2]; GPIO4 += j_exp[3]; GPIO5 += j_exp[4]
GPIO39 += j_exp[5]; GPIO40 += j_exp[6]; GPIO41 += j_exp[7]
GPIO42 += j_exp[8]; GPIO46 += j_exp[9]; GPIO3 += j_exp[10]

j_dbg = HDR1X4(); j_dbg.ref = "J6"; j_dbg.value = "UART_DBG"
GND += j_dbg[1]; GPIO43 += j_dbg[2]; GPIO44 += j_dbg[3]; P3V3 += j_dbg[4]

# テストポイント
tp1 = TP(); tp1.ref = "TP1"; P5V += tp1[1]
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TP_LIST = [
    (PN["A"]["TIP"],    "TIP_A"),     (PN["A"]["RING"],   "RING_A"),
    (FR_5V["A"],        "FR_A_5V"),   (RM_5V["A"],        "RM_A_5V"),
    (PN["A"]["SHKRAW"], "SHK_A_RAW"), (PN["A"]["VXPIN"],  "VX_A_PIN"),
    (PN["A"]["VRPIN"],  "VR_A_PIN"),  (PN["A"]["VXAUD"],  "VX_A_AUD"),
    (PN["B"]["TIP"],    "TIP_B"),     (PN["B"]["RING"],   "RING_B"),
    (FR_5V["B"],        "FR_B_5V"),   (RM_5V["B"],        "RM_B_5V"),
    (PN["B"]["SHKRAW"], "SHK_B_RAW"), (PN["B"]["VXPIN"],  "VX_B_PIN"),
    (PN["B"]["VRPIN"],  "VR_B_PIN"),  (PN["B"]["VXAUD"],  "VX_B_AUD"),
    (VIN_RAW,           "VIN_RAW"),   (VIN_F,             "VIN_F"),
    (VAUD,              "VAUD"),      (VREF165,           "VREF165"),
    (GND,               "GND"),
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# ===========================================================================
# 動作チェック用ステータス LED (D4-D9: ポート毎に HOOK / RING / LINK)
# ファームウェア変更不要のハードウェア連動表示。既存の D2 (電源) /
# D3 (GPIO4 ステータス) とは役割が別で、通電したまま各ポートの状態を
# 目視確認するためのもの。シルクに HOOK_x / RING_x / LINK_x の
# 役割ラベルを付ける (基板生成スクリプト側で配置)。
#
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
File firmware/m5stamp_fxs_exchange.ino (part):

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// ===========================================================================
// GPIO 定義 (DESIGN.md 6.2)
// ===========================================================================
static const int PIN_MON_A   = 1;   // ADC1_CH0 : ポートA 音声モニタ/DTMF
static const int PIN_MON_B   = 2;   // ADC1_CH1 : ポートB 音声モニタ/DTMF
static const int PIN_LED_ST  = 4;   // ステータス LED
static const int PIN_TONE    = 6;   // LEDC PWM 400Hz -> トーンバス
static const int PIN_SHK_A   = 7;   // ポートA フック検出 (分圧済 3.3V系)
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static const int PIN_FR_B    = 12;  // ポートB 極性/リング    -> HCT244
static const int PIN_SEL_A   = 13;  // ポートA 音声選択 (L=相手VX, H=トーン)
static const int PIN_SEL_B   = 14;  // ポートB 音声選択
static const int PIN_PD_EN   = 15;  // SLIC PD 引き下げ (2N7002 ゲート, 既定 OFF)

// ===========================================================================
// チューニング定数
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};

static Port ports[2] = {
  { "A", PIN_SHK_A, PIN_RM_A, PIN_FR_A, PIN_SEL_A, PIN_MON_A, false, false, 0, 0 },
  { "B", PIN_SHK_B, PIN_RM_B, PIN_FR_B, PIN_SEL_B, PIN_MON_B, false, false, 0, 0 },
};

// SHK を読んでデバウンス済 hook を更新する
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  }
  pinMode(PIN_LED_ST, OUTPUT);
  digitalWrite(PIN_LED_ST, LOW);
  pinMode(PIN_PD_EN, OUTPUT);
  digitalWrite(PIN_PD_EN, LOW);         // 2N7002 OFF = PD 無効 (モジュール常時ON)

  // トーン PWM (LEDC 互換シム経由, core 2.x/3.x 両対応)
  toneLedcAttach();
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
